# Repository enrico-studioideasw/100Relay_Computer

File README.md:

# 100Relay_Computer
A full calculator made with 100 relays 

Questo repository raccoglie lo sviluppo di un computer a relè realizzato con componenti facilmente reperibili. L'obiettivo non è ottenere prestazioni, ma costruire una macchina didattica completamente comprensibile: dalla logica cablata al microcodice, fino all'assembler e ai programmi di esempio.

Nella documentazione troverete foto, schema a blocchi della macchina, pcb e sch per eagle. 

Il risultato è:
Una scheda madre che raccoglie tutti i componenti separandone le unità logiche.
Una macchina con un microcodice minimale ma computazionalmente completo.
32 bytes di rom e 4 nibbles di ram (potenzialmente espandibili a 16). Programma in rome  ram per i dati. Nessun I/O ma un led per ciascuna cella di ram. 
Mantenendo la soglia dei 100 rele non credo sia possibile fare di meglio.

Semplificazioni:
I rele sono usati con logica positiva: "1" se c'e' abbastanza tensione da far scattare la bobina, "0" in tutti gli altri casi. Questo semplifica molto la progettazione.. e permette di abbinare facilmente OR e AND a diodi,  principalmente utilizzati per il microcodice.
La micro-ROM è realizzata mediante una matrice di socket femmina passo 2,54 mm. Il contenuto della ROM viene programmato inserendo o rimuovendo diodi nei socket, senza necessità di saldature e con il programma "a vista". 

Il mio scopo era stare sotto i  100 rele, usando componenti commerciali a basso costo. Ad oggi:
 4 rele DPDT per il clock a più fasi
12 rele DPDT per il program counter a 6 bit
19 rele per pilotare la ROM "a diodi". 
24 rele per la ram e 4 per la sua decodifica
18 rele per accumulatore, risultato, Instruction Register.
12 rele per la ALU
Il resto per microcodice e logiche varie. Quindi scopo non raggiunto ma macchina completa con esattamente 100 rele. Potremmo averne circa 90 con solo 16 bytes di rom, ma si rinuncia alla possibilita di programmi decenti. 

Ho dovuto ridurre all'osso il microcodice, quindi queste sono le Istruzioni:
HCF      0000XXXX (oops.. HALT) 
JZ DEST  11XXXXXX
LD       0110XXXX Load direct, azzera flag 
LDA      0100XXXX Load from ram addr 
SUM      0111XXXX somma ad A il conentuto della cella XXXX 
STA      1000XXXX copia A sulla cella indicata di ram

Una cella di ROM vuota causa immediatamente un HALT,  quindi senza programma la macchian si ferma subito (Halt and Catch Fire ..  forse)

Note:
- per decrementare A basta sommare F. 
- Per una jump basta qualcosa tipo: STA 3, LD 0, JZ XX, LDA 3  .. non ho uno stack ma qualcosa per mantenere A si fa lo stesso. Certo che più ram saebbe meglio.

qualche demo:
Faccina sorridente sui led di stato della ram:

LD 9
STA 0
LD 0
STA 1
LD 9
STA 2
LD 6
STA 3
HCF (oops.. HALT) 

Diagonale

LD 8
STA 0
LD 4
STA 1
LD 2
STA 2
LD 1
STA 3
HCF

Prodotto:
RAM0 = moltiplicando
RAM1 = moltiplicatore
RAM2 = risultato
RAMF = 15 (-1)
00 LD 0
01 STA 2          ; risultato = 0
LOOP:
02 LDA 1
03 JZ 13 - END          ; finito?
04 STA 3          ; salvo contatore
05 LDA 2
06 SUM 0
07 STA 2          ; risultato += moltiplicando
08 LDA 3
09 SUM F
10 STA 1          ; contatore--
11 JMP 02 LOOP
12 END: HCF (oops.. halt)

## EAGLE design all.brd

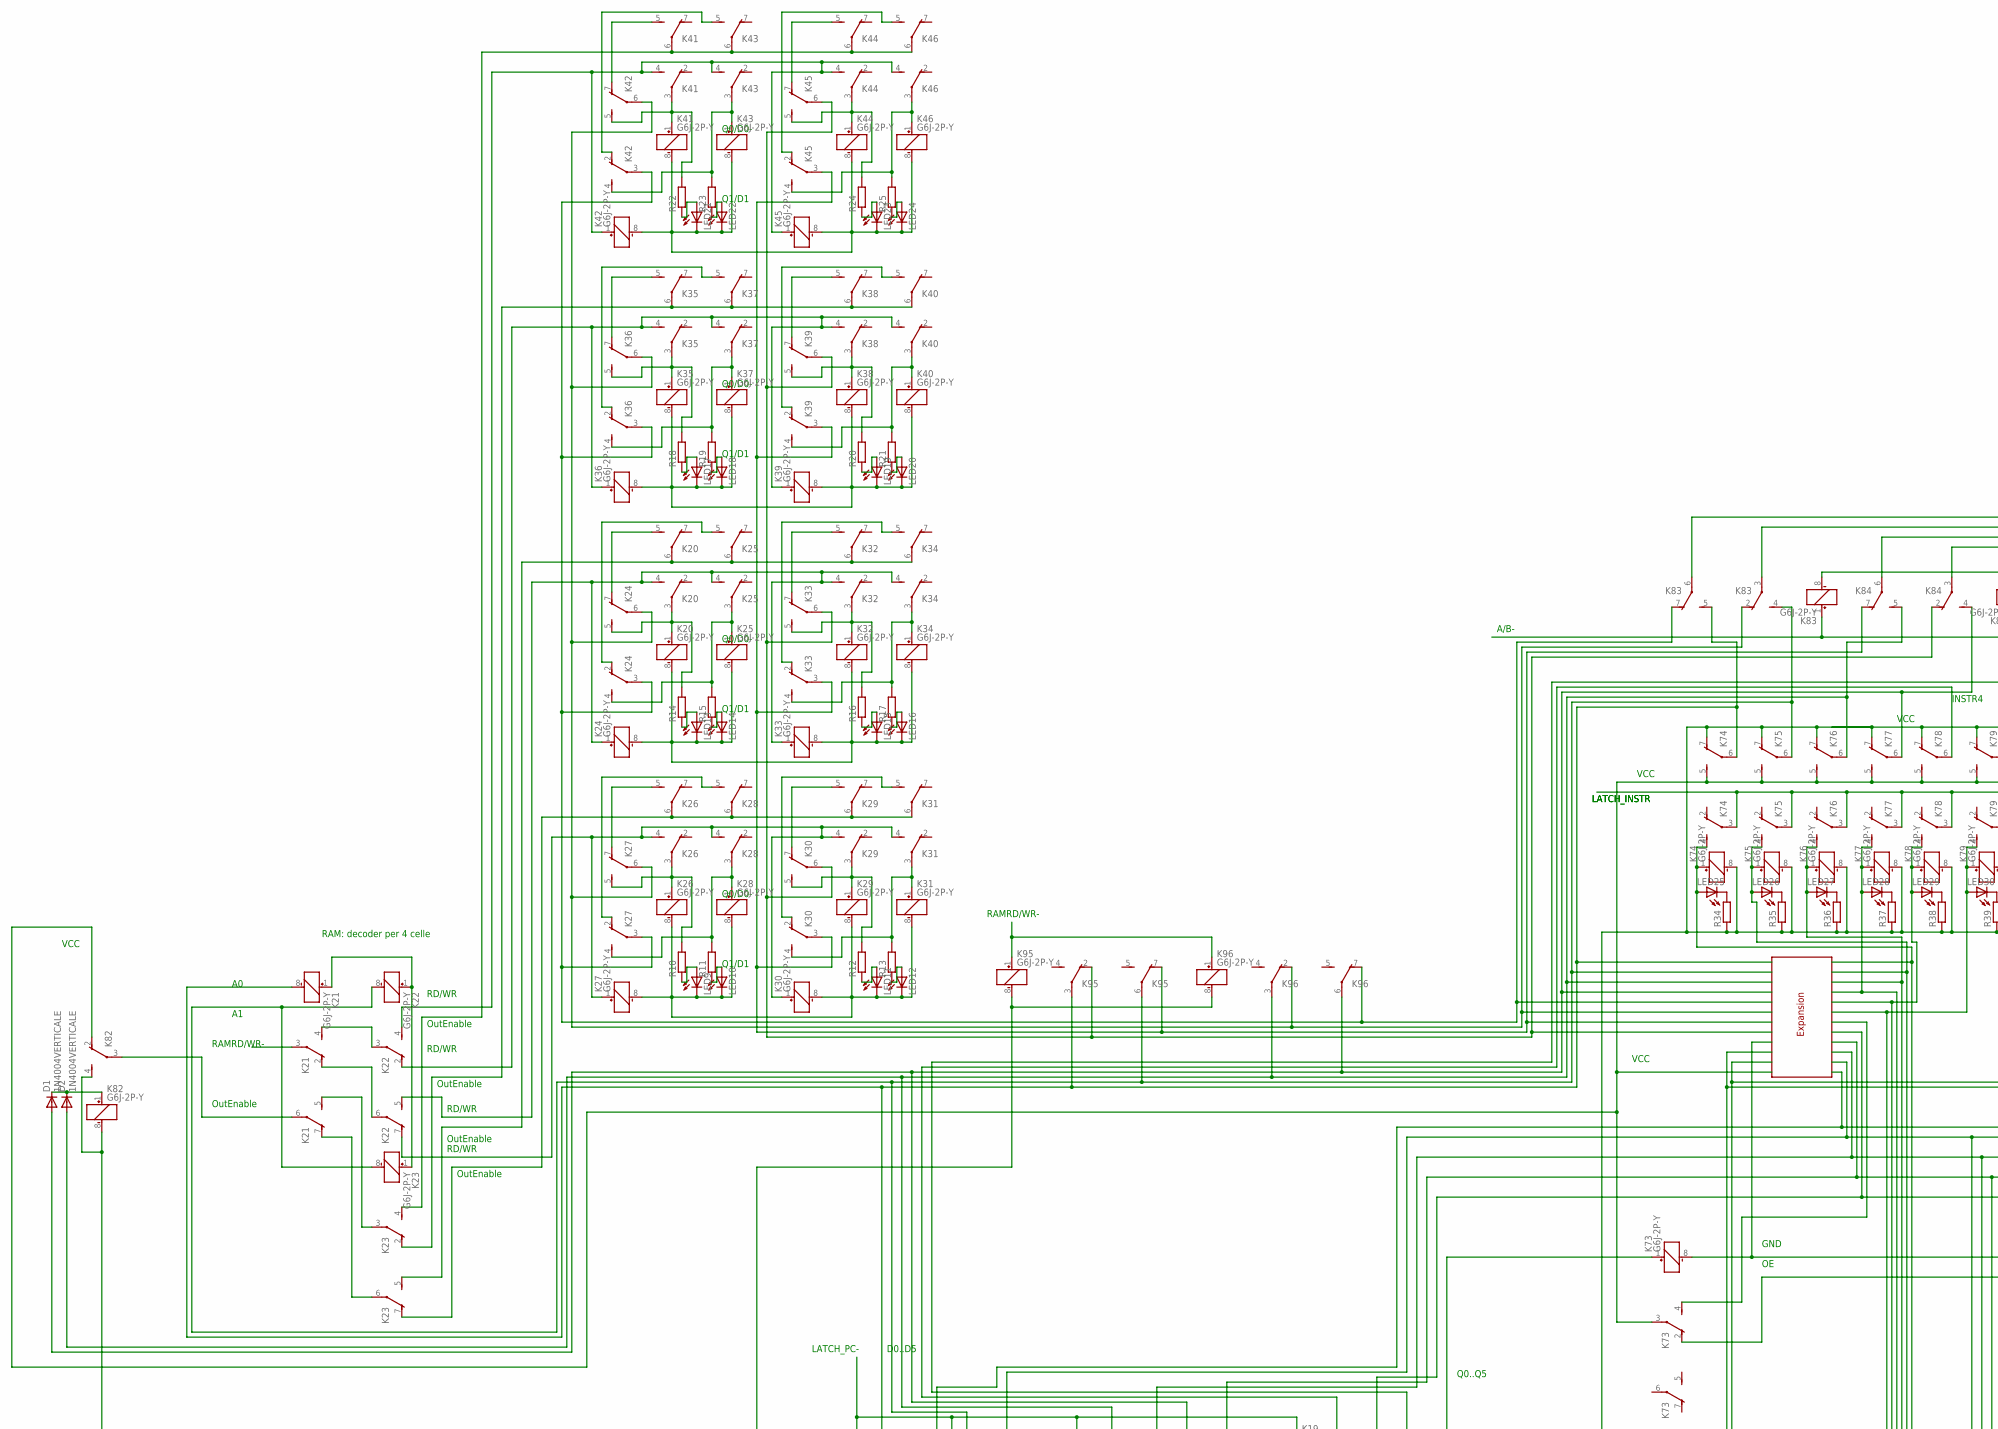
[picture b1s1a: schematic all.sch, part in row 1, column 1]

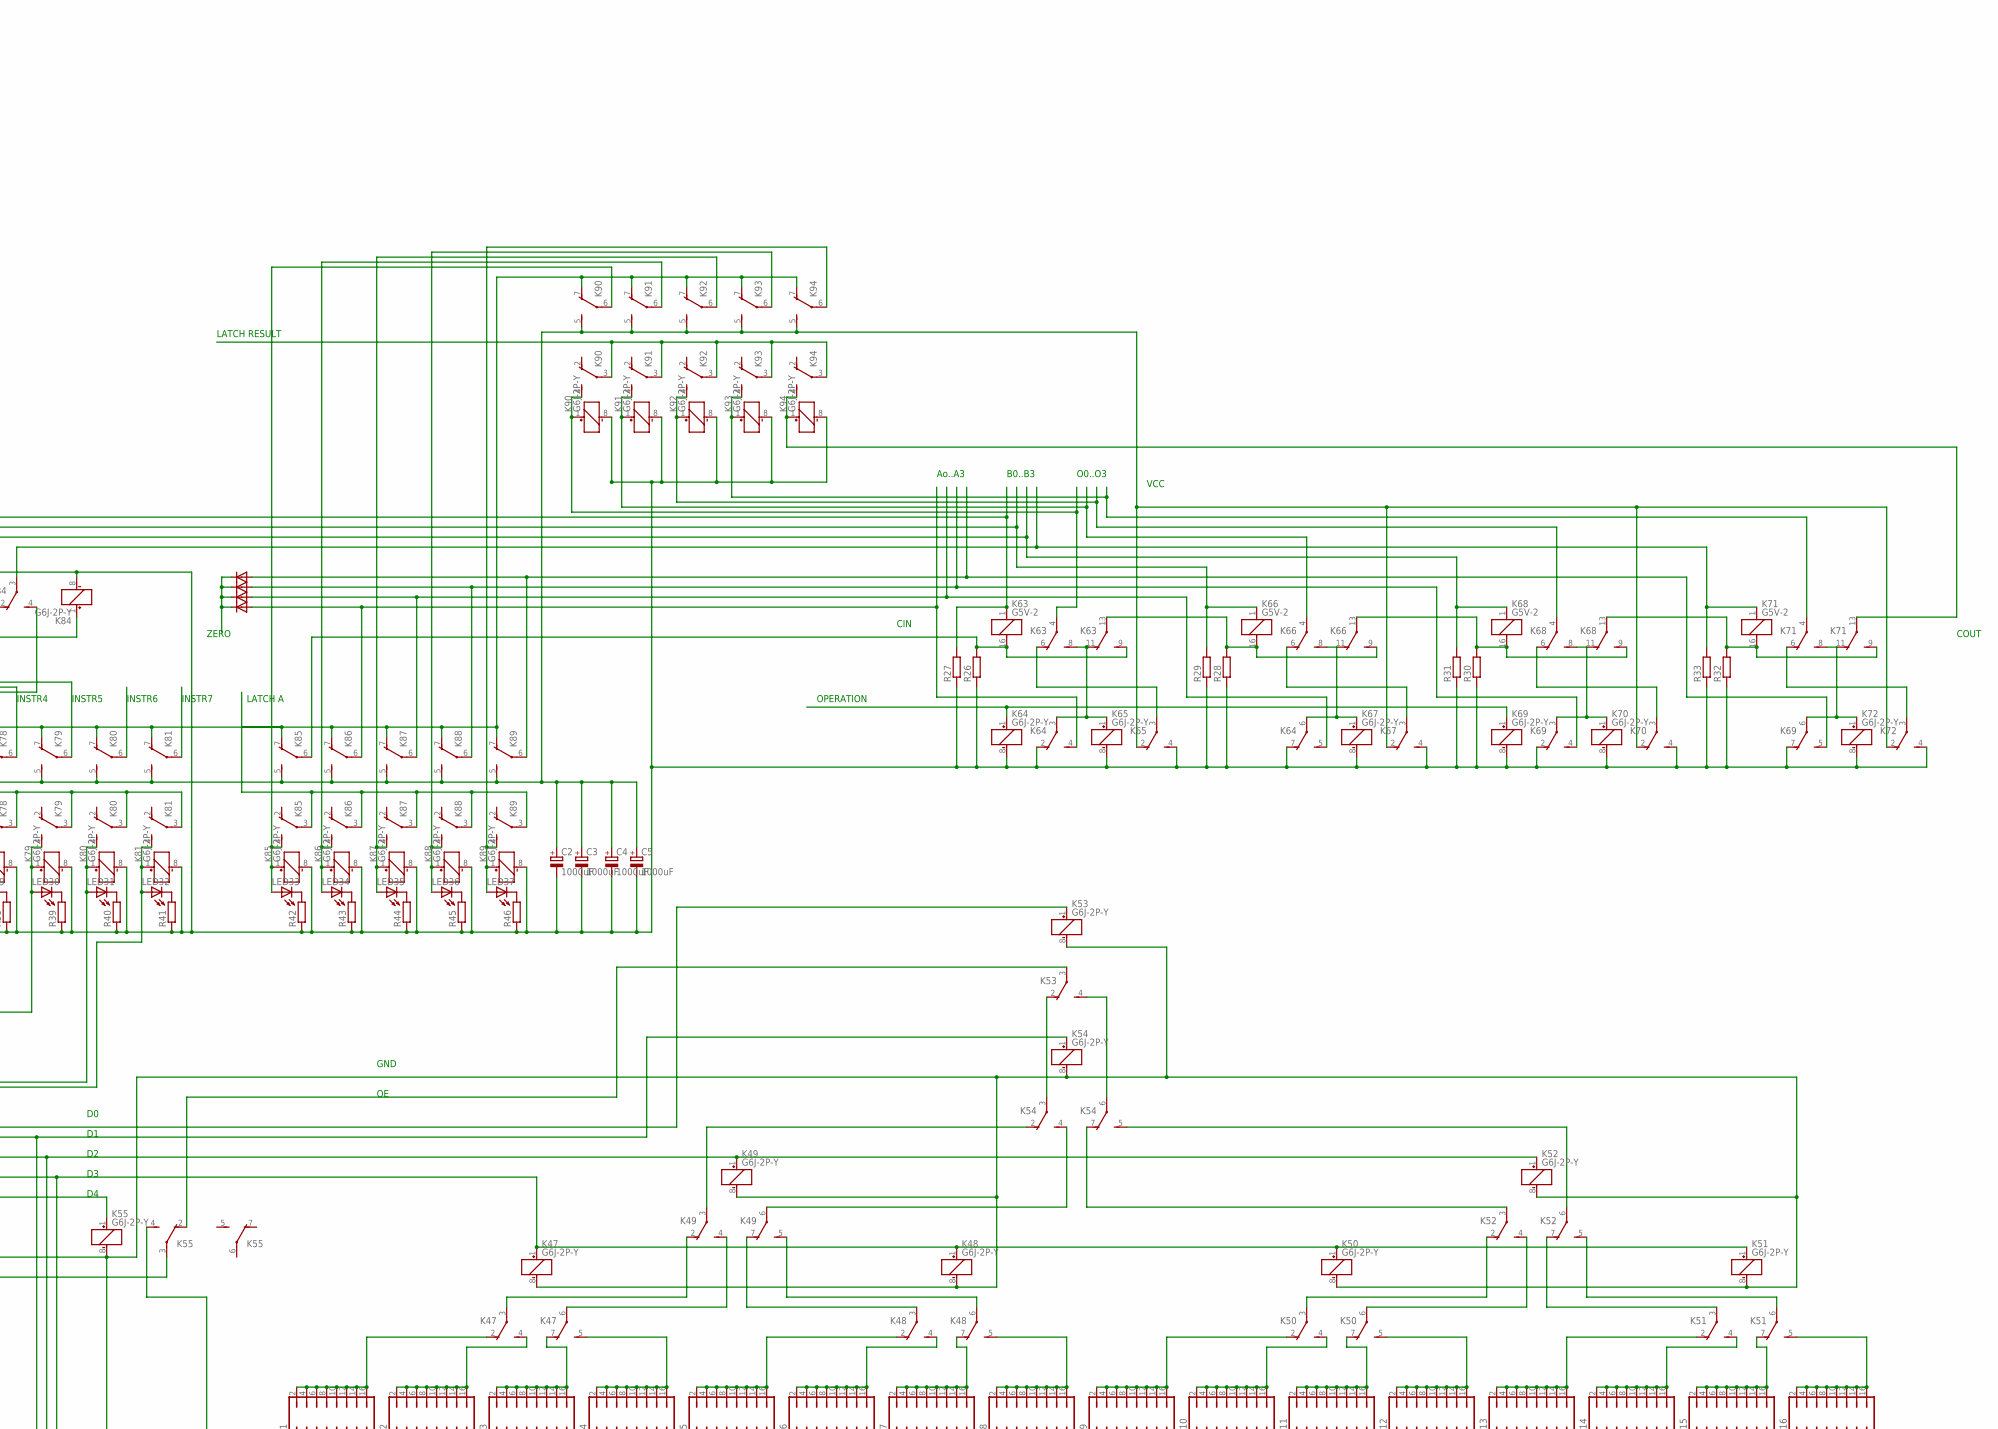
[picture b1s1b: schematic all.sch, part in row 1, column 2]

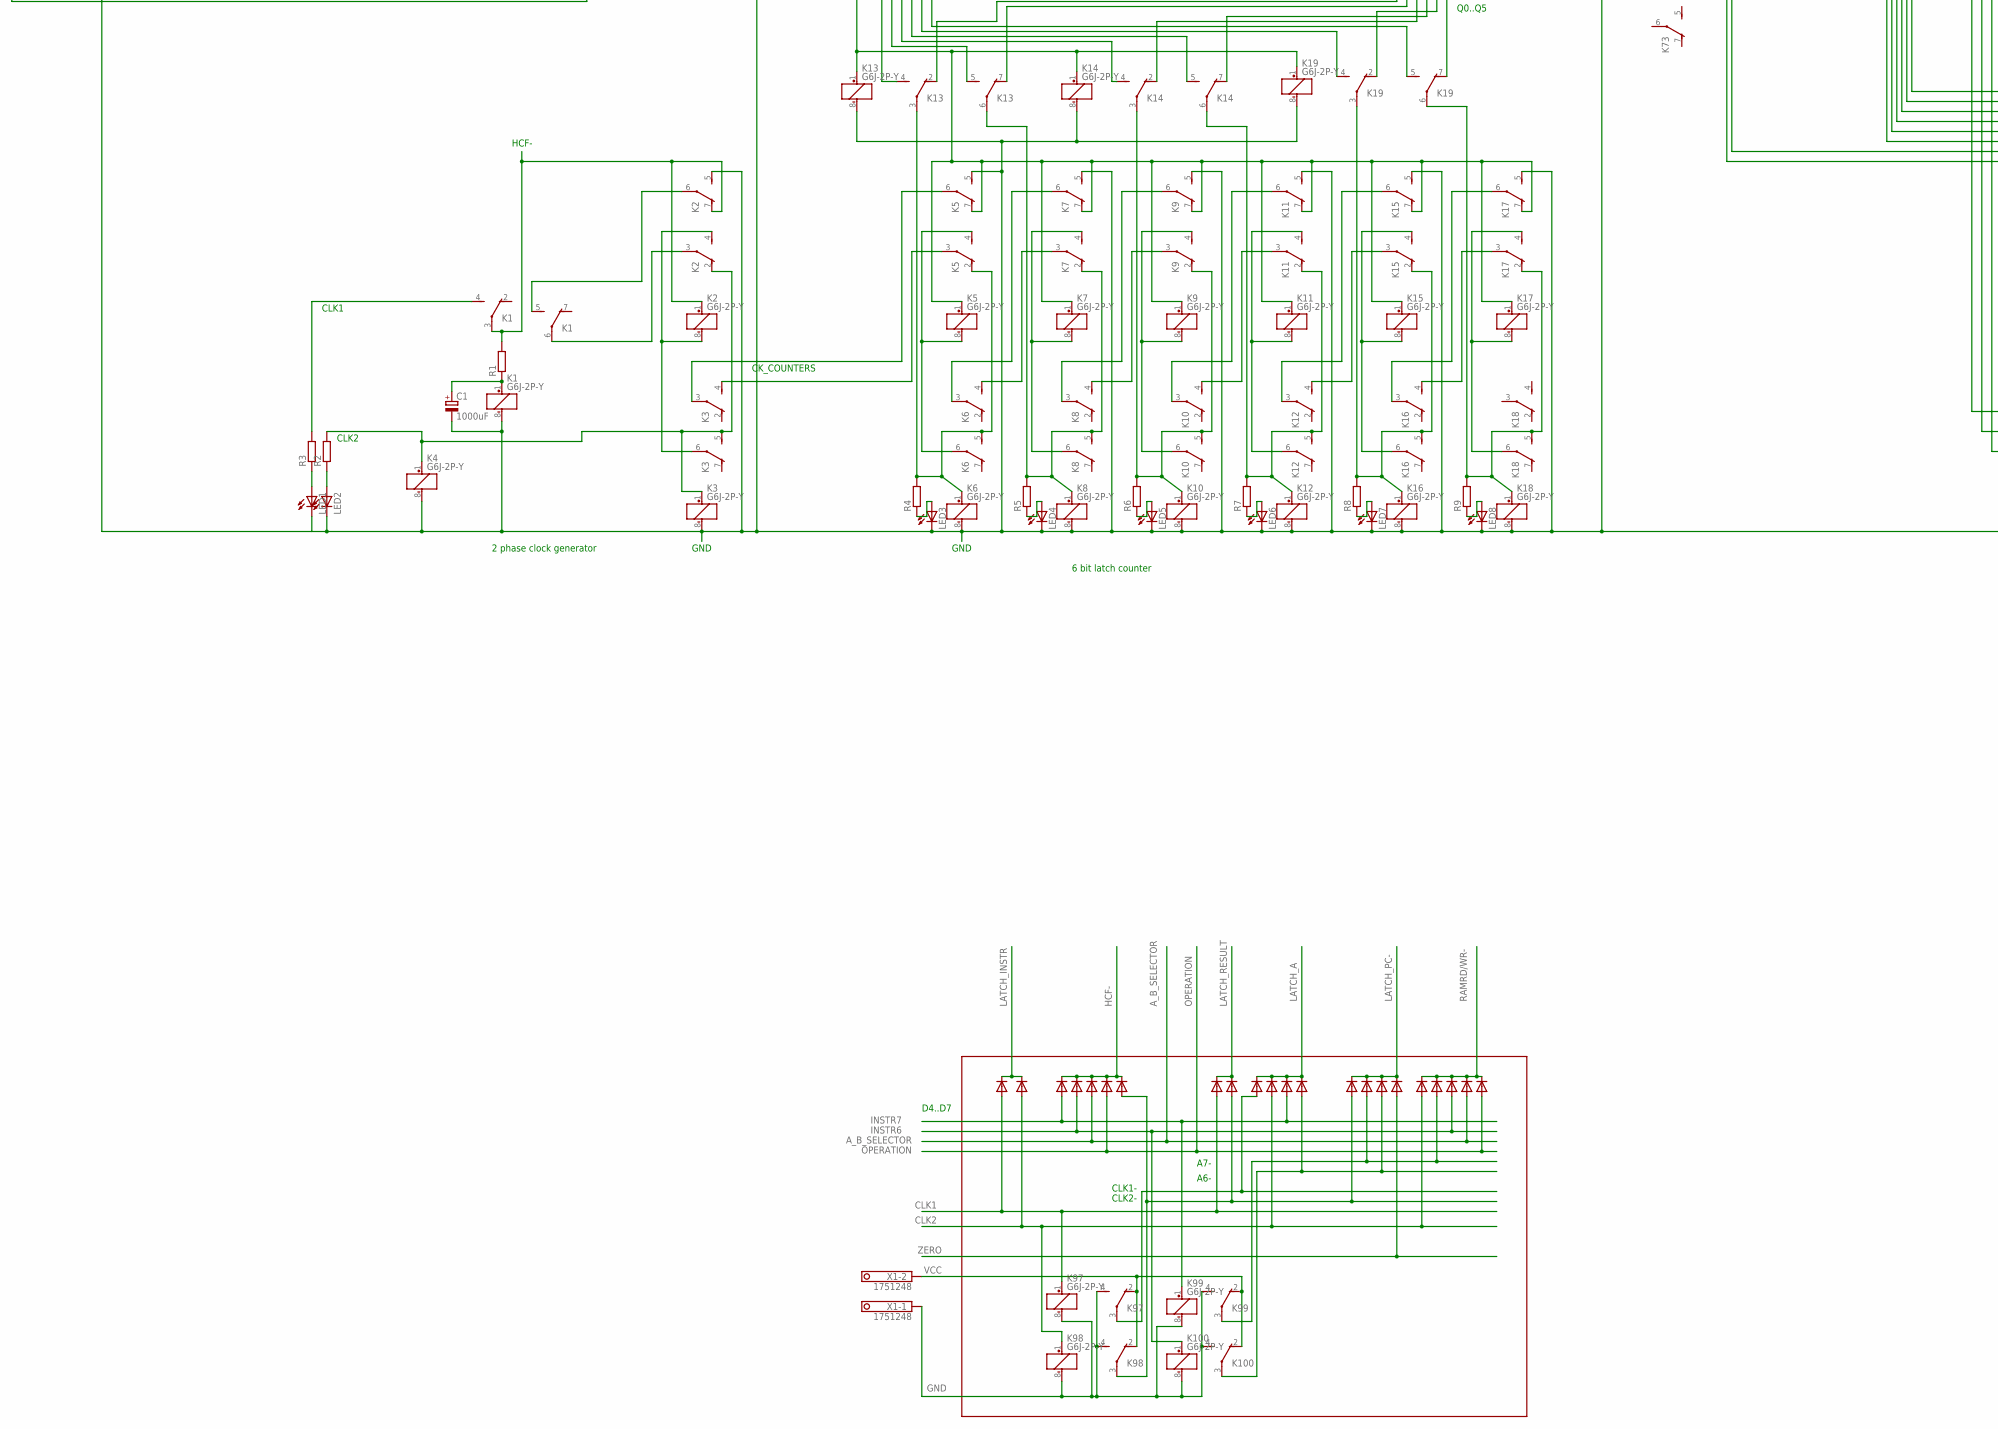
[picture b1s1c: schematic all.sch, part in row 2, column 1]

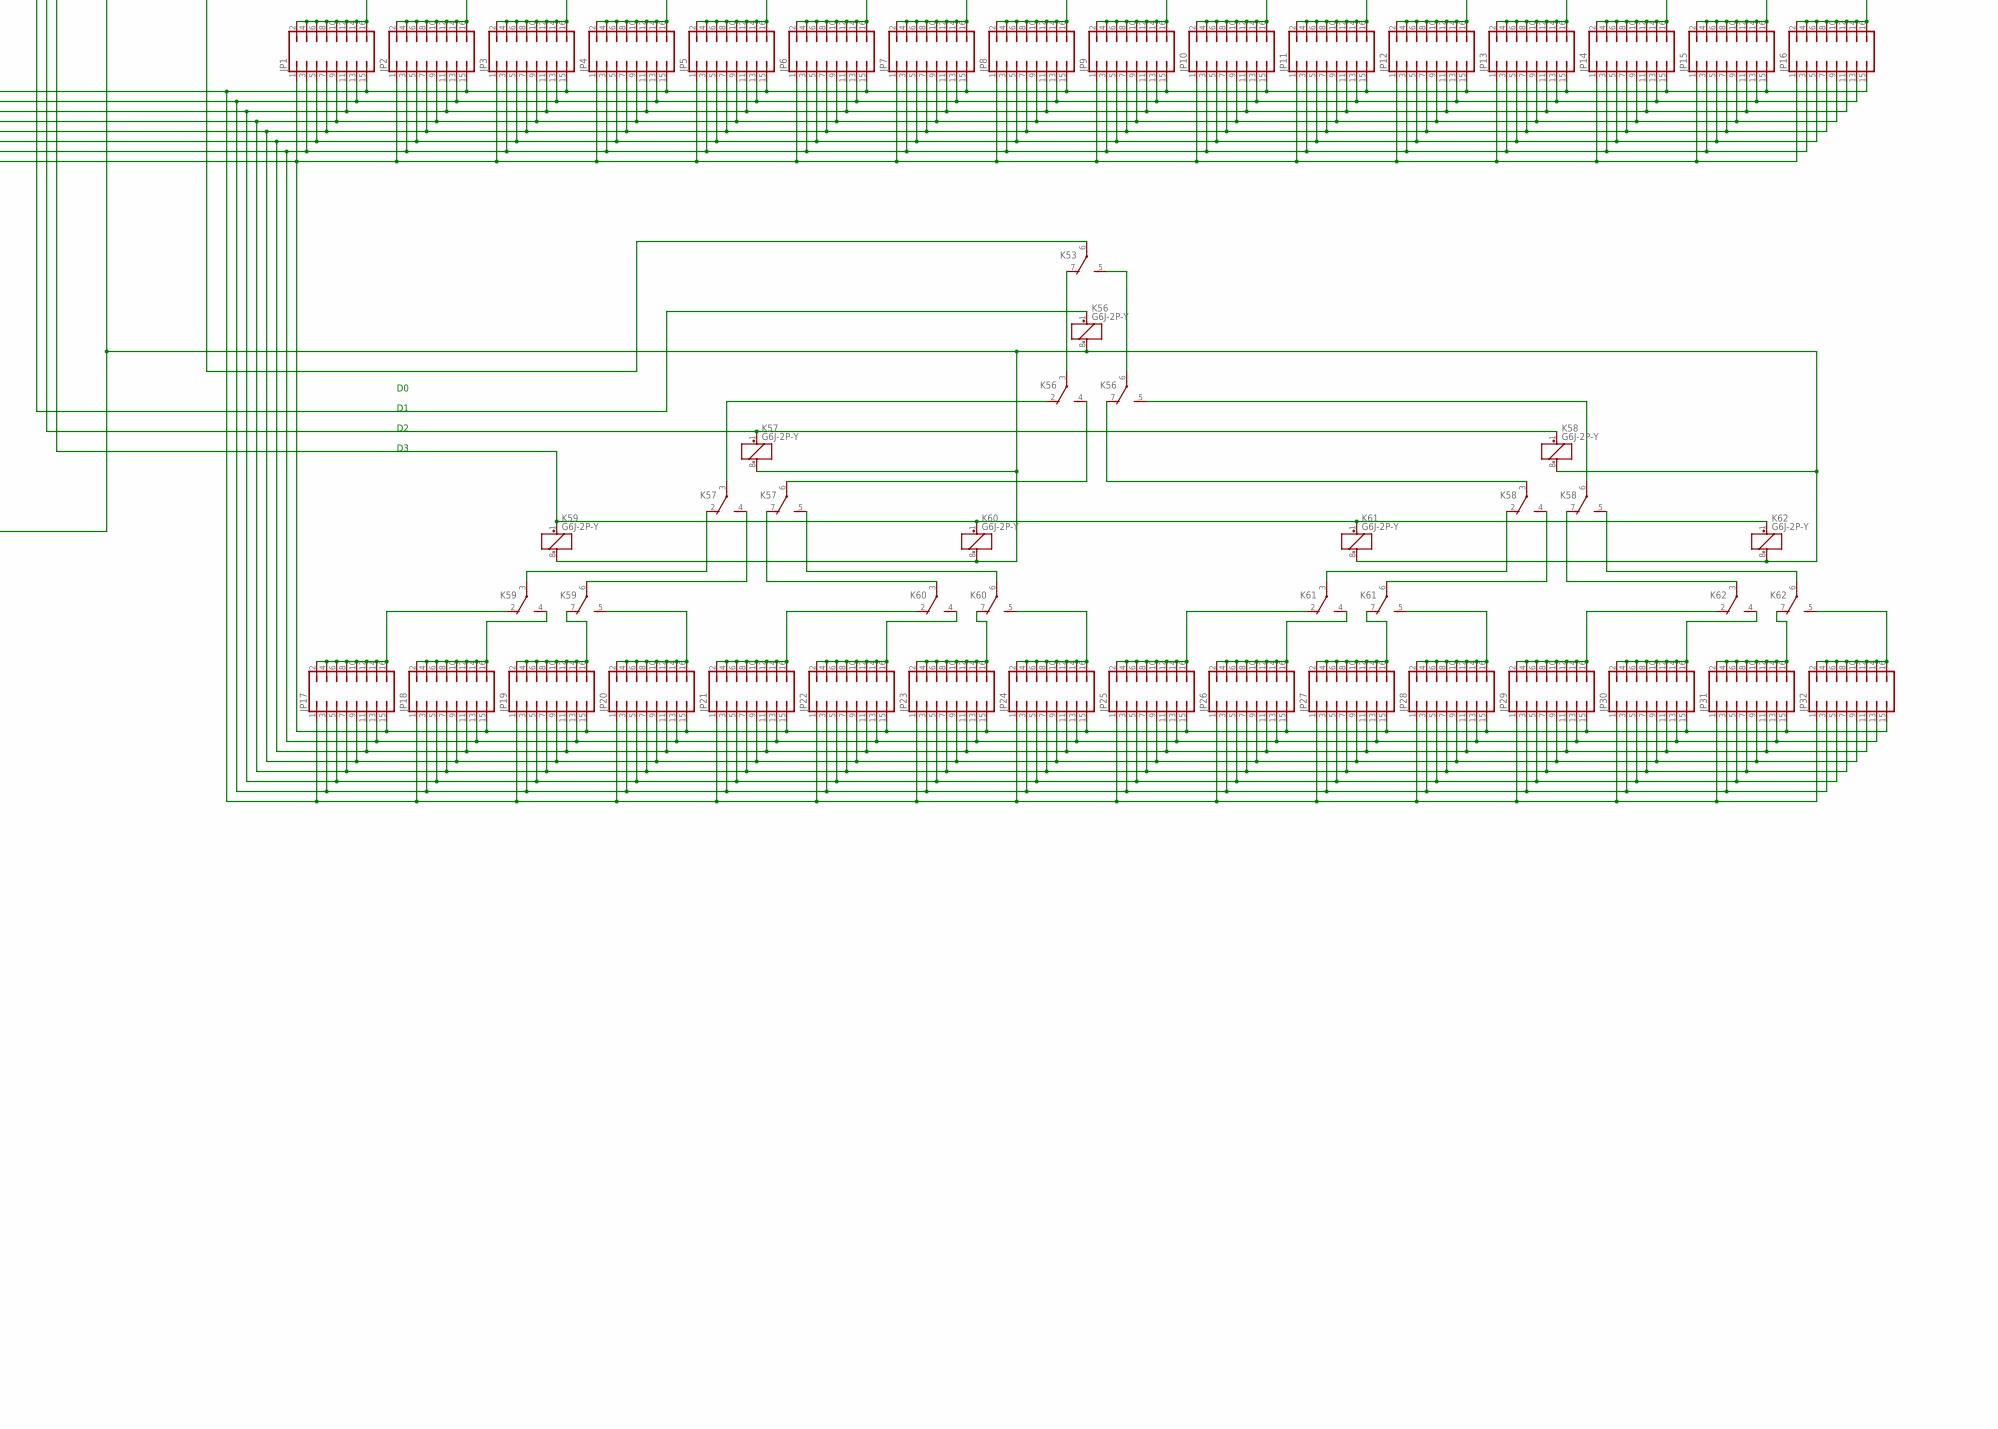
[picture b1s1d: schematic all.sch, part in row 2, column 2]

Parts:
C1: 1000uF; E5-10,5
C2, C3, C4, C5: 1000uF; E3,5-10
D1, D2, D3, D4, D5, D6, D29, D30, D31, D32, D33, D34, D35, D36, D37, D38, D39, D40, D41, D42, D43, D44, D45, D46, D47, D48, D49, D50: 1N4004VERTICALE; ZDIO-2.5
JP1, JP2, JP3, JP4, JP5, JP6, JP7, JP8, JP9, JP10, JP11, JP12, JP13, JP14, JP15, JP16, JP17, JP18, JP19, JP20, JP21, JP22, JP23, JP24, JP25, JP26, JP27, JP28, JP29, JP30, JP31, JP32: JP8Q
K1, K2, K3, K4, K5, K6, K7, K8, K9, K10, K11, K12, K13, K14, K15, K16, K17, K18, K19, K20, K21, K22, K23, K24, K25, K26, K27, K28, K29, K30, K31, K32, K33, K34, K35, K36, K37, K38, K39, K40, K41, K42, K43, K44, K45, K46, K47, K48, K49, K50, K51, K52, K53, K54, K55, K56, K57, K58, K59, K60, K61, K62, K64, K65, K67, K69, K70, K72, K73, K74, K75, K76, K77, K78, K79, K80, K81, K82, K83, K84, K85, K86, K87, K88, K89, K90, K91, K92, K93, K94, K95, K96, K97, K98, K99, K100: G6J-2P-Y
K63, K66, K68, K71: G5V-2
LED1, LED2, LED3, LED4, LED5, LED6, LED7, LED8, LED9, LED10, LED11, LED12, LED13, LED14, LED15, LED16, LED17, LED18, LED19, LED20, LED21, LED22, LED23, LED24: LED5MM
LED25, LED26, LED27, LED28, LED29, LED30, LED31, LED32, LED33, LED34, LED35, LED36, LED37: LED3MM
R1, R2, R3, R4, R5, R6, R7, R8, R9, R10, R11, R12, R13, R14, R15, R16, R17, R18, R19, R20, R21, R22, R23, R24, R25, R26, R27, R28, R29, R30, R31, R32, R33, R34, R35, R36, R37, R38, R39, R40, R41, R42, R43, R44, R45, R46: R-EU_0204/2V; 0204V
X1: 1751248

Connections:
A_B_SELECTOR: D33.A, D49.A, K83.1 (+), K84.1 (+)
CLK1: D29.A, D36.A, K1.4 (S), K97.1 (+), R3.2
CLK2: D30.A, D39.A, D46.A, K2.2 (O), K3.1 (+), K3.5 (S), K4.1 (+), K98.1 (+), R2.2
GND: C1.-, C2.-, C3.-, C4.-, C5.-, K1.8 (-), K2.5 (S), K3.8 (-), K4.8 (-), K5.5 (S), K6.8 (-), K7.5 (S), K8.8 (-), K9.5 (S), K10.8 (-), K11.5 (S), K12.8 (-), K13.8 (-), K14.8 (-), K15.5 (S), K16.8 (-), K17.5 (S), K18.8 (-), K19.8 (-), K47.8 (-), K48.8 (-), K49.8 (-), K50.8 (-), K51.8 (-), K52.8 (-), K53.8 (-), K54.8 (-), K55.8 (-), K56.8 (-), K57.8 (-), K58.8 (-), K59.8 (-), K60.8 (-), K61.8 (-), K62.8 (-), K64.2 (O), K64.7 (O), K64.8 (-), K65.4 (S), K65.8 (-), K67.4 (S), K67.8 (-), K69.2 (O), K69.7 (O), K69.8 (-), K70.4 (S), K70.8 (-), K72.4 (S), K72.8 (-), K73.8 (-), K74.7 (O), K74.8 (-), K75.7 (O), K75.8 (-), K76.7 (O), K76.8 (-), K77.7 (O), K77.8 (-), K78.7 (O), K78.8 (-), K79.7 (O), K79.8 (-), K80.7 (O), K80.8 (-), K81.7 (O), K81.8 (-), K82.4 (S), K82.8 (-), K83.8 (-), K84.8 (-), K85.7 (O), K85.8 (-), K86.7 (O), K86.8 (-), K87.7 (O), K87.8 (-), K88.7 (O), K88.8 (-), K89.7 (O), K89.8 (-), K90.7 (O), K90.8 (-), K91.7 (O), K91.8 (-), K92.7 (O), K92.8 (-), K93.7 (O), K93.8 (-), K94.7 (O), K94.8 (-), K95.8 (-), K96.8 (-), K97.4 (S), K97.8 (-), K98.4 (S), K98.8 (-), K99.4 (S), K99.8 (-), K100.4 (S), K100.8 (-), LED1.K (C), LED2.K (C), LED3.K (C), LED4.K (C), LED5.K (C), LED6.K (C), LED7.K (C), LED8.K (C), R26.1, R27.1, R28.1, R29.1, R30.1, R31.1, R32.1, R33.1, R34.1, R35.1, R36.1, R37.1, R38.1, R39.1, R40.1, R41.1, R42.1, R43.1, R44.1, R45.1, R46.1, X1.1
HCF-: D31.C, D32.C, D33.C, D34.C, D35.C, K1.3, K2.1 (+), K2.7 (O), R1.2
INSTR4: K19.4 (S), K78.6
INSTR5: K19.5 (S), K79.6
INSTR6: D32.A, D48.A, K80.6, K100.1 (+)
INSTR7: D31.A, D40.A, K81.6, K99.1 (+)
LATCH_A: D38.C, D39.C, D40.C, D41.C, K85.3, K86.3, K87.3, K88.3, K89.3
LATCH_INSTR: D29.C, D30.C, K74.3, K75.3, K76.3, K77.3, K78.3, K79.3, K80.3, K81.3
LATCH_PC-: D42.C, D43.C, D44.C, D45.C, K5.1 (+), K5.7 (O), K7.1 (+), K7.7 (O), K9.1 (+), K9.7 (O), K11.1 (+), K11.7 (O), K13.1 (+), K14.1 (+), K15.1 (+), K15.7 (O), K17.1 (+), K17.7 (O), K19.1 (+)
LATCH_RESULT: D36.C, D37.C, K90.3, K91.3, K92.3, K93.3, K94.3
unnamed: C1.+, K1.1 (+), R1.1
unnamed: K6.3, K7.6
unnamed: K6.4 (S), K7.3
unnamed: K1.5 (S), K2.6
unnamed: K1.6, K2.3
unnamed: D38.A, K97.3
unnamed: K63.9 (S), K63.16 (2), K85.6, R26.2
unnamed: D35.A, D37.A, D42.A, K98.3
unnamed: K2.4 (S), K2.8 (-), K3.6
unnamed: K3.4 (S), K5.3
unnamed: K3.3, K5.6
unnamed: K13.4 (S), K21.8 (-), K74.6, K83.5 (S), K95.3
unnamed: K19.2 (O), K55.1 (+)
unnamed: K12.3, K15.6
unnamed: K13.7 (O), K54.1 (+), K56.1 (+)
unnamed: K12.4 (S), K15.3
unnamed: K5.2 (O), K6.1 (+), K6.5 (S), K13.3, R4.2
unnamed: K5.4 (S), K5.8 (-), K6.6
unnamed: K13.5 (S), K22.8 (-), K23.8 (-), K75.6, K83.4 (S), K95.6
unnamed: K13.2 (O), K53.1 (+)
unnamed: D2.A, K14.4 (S), K76.6, K84.5 (S), K96.3
unnamed: K7.2 (O), K8.1 (+), K8.5 (S), K13.6, R5.2
unnamed: K7.4 (S), K7.8 (-), K8.6
unnamed: D1.A, K14.5 (S), K77.6, K84.4 (S), K96.6
unnamed: K14.2 (O), K49.1 (+), K52.1 (+), K57.1 (+), K58.1 (+)
unnamed: K8.3, K9.6
unnamed: K8.4 (S), K9.3
unnamed: K14.7 (O), K47.1 (+), K48.1 (+), K50.1 (+), K51.1 (+), K59.1 (+), K60.1 (+), K61.1 (+), K62.1 (+)
unnamed: K15.2 (O), K16.1 (+), K16.5 (S), K19.3, R8.2
unnamed: K9.2 (O), K10.1 (+), K10.5 (S), K14.3, R6.2
unnamed: K9.4 (S), K9.8 (-), K10.6
unnamed: K15.4 (S), K15.8 (-), K16.6
unnamed: K16.3, K17.6
unnamed: K10.3, K11.6
unnamed: K10.4 (S), K11.3
unnamed: K16.4 (S), K17.3
unnamed: K11.2 (O), K12.1 (+), K12.5 (S), K14.6, R7.2
unnamed: K11.4 (S), K11.8 (-), K12.6
unnamed: K19.7 (O), K73.1 (+)
unnamed: LED1.A, R3.1
unnamed: LED2.A, R2.1
unnamed: K17.2 (O), K18.1 (+), K18.5 (S), K19.6, R9.2
unnamed: K17.4 (S), K17.8 (-), K18.6
unnamed: LED9.A, R10.1
unnamed: D43.A, D47.A, K99.3
unnamed: D41.A, D44.A, K100.3
unnamed: LED3.A, R4.1
unnamed: LED4.A, R5.1
unnamed: LED5.A, R6.1
unnamed: LED6.A, R7.1
unnamed: LED7.A, R8.1
unnamed: LED8.A, R9.1
unnamed: LED10.A, R11.1
unnamed: LED11.A, R12.1
unnamed: LED12.A, R13.1
unnamed: K21.4 (S), K22.3
unnamed: K21.2 (O), K22.6
unnamed: K86.1 (+), K86.4 (S), K91.6, LED34.A
unnamed: K22.2 (O), K35.4 (S), K36.1 (+), K37.4 (S), K38.4 (S), K39.1 (+), K40.4 (S)
unnamed: K20.4 (S), K22.5 (S), K24.1 (+), K25.4 (S), K32.4 (S), K33.1 (+), K34.4 (S)
unnamed: K22.7 (O), K26.4 (S), K27.1 (+), K28.4 (S), K29.4 (S), K30.1 (+), K31.4 (S)
unnamed: K21.5 (S), K23.3
unnamed: K21.7 (O), K23.6
unnamed: K63.1, K83.6, R27.2
unnamed: K23.2 (O), K35.6, K37.6, K38.6, K40.6
unnamed: D6.A, K64.4 (S), K86.6
unnamed: K23.7 (O), K26.6, K28.6, K29.6, K31.6
unnamed: K21.6, K82.3
unnamed: K21.1 (+), K22.1 (+), K23.1 (+)
unnamed: K22.4 (S), K41.4 (S), K42.1 (+), K43.4 (S), K44.4 (S), K45.1 (+), K46.4 (S)
unnamed: K23.4 (S), K41.6, K43.6, K44.6, K46.6
unnamed: JP1.2, JP1.4, JP1.6, JP1.8, JP1.10, JP1.12, JP1.14, JP1.16, K47.2 (O)
unnamed: K20.6, K23.5 (S), K25.6, K32.6, K34.6
unnamed: K20.1 (+), K20.3, K24.5 (S), R14.2
unnamed: K26.1 (+), K26.3, K27.5 (S), R10.2
unnamed: K24.2 (O), K25.5 (S)
unnamed: K24.4 (S), K25.1 (+), K25.3, R15.2
unnamed: K20.5 (S), K24.7 (O)
unnamed: K27.2 (O), K28.5 (S)
unnamed: K27.4 (S), K28.1 (+), K28.3, R11.2
unnamed: K26.5 (S), K27.7 (O)
unnamed: K24.6, K27.6, K36.6, K42.6, K83.2 (O), K96.2 (O)
unnamed: K24.3, K27.3, K36.3, K42.3, K83.7 (O), K96.7 (O)
unnamed: K29.1 (+), K29.3, K30.5 (S), R12.2
unnamed: K26.8 (-), K27.8 (-), K28.8 (-), K29.8 (-), K30.8 (-), K31.8 (-), LED9.K (C), LED10.K (C), LED11.K (C), LED12.K (C)
unnamed: JP2.2, JP2.4, JP2.6, JP2.8, JP2.10, JP2.12, JP2.14, JP2.16, K47.4 (S)
unnamed: JP3.2, JP3.4, JP3.6, JP3.8, JP3.10, JP3.12, JP3.14, JP3.16, K47.7 (O)
unnamed: K30.2 (O), K31.5 (S)
unnamed: K30.4 (S), K31.1 (+), K31.3, R13.2
unnamed: K29.5 (S), K30.7 (O)
unnamed: K30.6, K33.6, K39.6, K45.6, K84.2 (O), K95.2 (O)
unnamed: K30.3, K33.3, K39.3, K45.3, K84.7 (O), K95.7 (O)
unnamed: K32.1 (+), K32.3, K33.5 (S), R16.2
unnamed: K20.8 (-), K24.8 (-), K25.8 (-), K32.8 (-), K33.8 (-), K34.8 (-), LED13.K (C), LED14.K (C), LED15.K (C), LED16.K (C)
unnamed: K33.2 (O), K34.5 (S)
unnamed: K33.4 (S), K34.1 (+), K34.3, R17.2
unnamed: K32.5 (S), K33.7 (O)
unnamed: JP4.2, JP4.4, JP4.6, JP4.8, JP4.10, JP4.12, JP4.14, JP4.16, K47.5 (S)
unnamed: JP5.2, JP5.4, JP5.6, JP5.8, JP5.10, JP5.12, JP5.14, JP5.16, K48.2 (O)
unnamed: LED13.A, R14.1
unnamed: LED14.A, R15.1
unnamed: LED15.A, R16.1
unnamed: LED16.A, R17.1
unnamed: JP8.2, JP8.4, JP8.6, JP8.8, JP8.10, JP8.12, JP8.14, JP8.16, K48.5 (S)
unnamed: JP7.2, JP7.4, JP7.6, JP7.8, JP7.10, JP7.12, JP7.14, JP7.16, K48.7 (O)
unnamed: K35.1 (+), K35.3, K36.5 (S), R18.2
unnamed: K36.2 (O), K37.5 (S)
unnamed: K36.4 (S), K37.1 (+), K37.3, R19.2
unnamed: K35.5 (S), K36.7 (O)
unnamed: JP6.2, JP6.4, JP6.6, JP6.8, JP6.10, JP6.12, JP6.14, JP6.16, K48.4 (S)
unnamed: K47.6, K49.4 (S)
unnamed: K38.1 (+), K38.3, K39.5 (S), R20.2
unnamed: K35.8 (-), K36.8 (-), K37.8 (-), K38.8 (-), K39.8 (-), K40.8 (-), LED17.K (C), LED18.K (C), LED19.K (C), LED20.K (C)
unnamed: K39.2 (O), K40.5 (S)
unnamed: K39.4 (S), K40.1 (+), K40.3, R21.2
unnamed: K38.5 (S), K39.7 (O)
unnamed: K47.3, K49.2 (O)
unnamed: K48.3, K49.7 (O)
unnamed: LED17.A, R18.1
unnamed: LED18.A, R19.1
unnamed: LED19.A, R20.1
unnamed: LED20.A, R21.1
unnamed: K48.6, K49.5 (S)
unnamed: K55.3, K73.2 (O)
unnamed: K41.1 (+), K41.3, K42.5 (S), R22.2
unnamed: K42.2 (O), K43.5 (S)
unnamed: K42.4 (S), K43.1 (+), K43.3, R23.2
unnamed: K41.5 (S), K42.7 (O)
unnamed: K63.8 (S), K63.11 (O), K64.3, K65.1 (+)
unnamed: K44.1 (+), K44.3, K45.5 (S), R24.2
unnamed: K41.8 (-), K42.8 (-), K43.8 (-), K44.8 (-), K45.8 (-), K46.8 (-), LED21.K (C), LED22.K (C), LED23.K (C), LED24.K (C)
unnamed: K45.2 (O), K46.5 (S)
unnamed: K45.4 (S), K46.1 (+), K46.3, R25.2
unnamed: K44.5 (S), K45.7 (O)
unnamed: K63.4, K90.1 (+), K90.4 (S)
unnamed: K63.6 (O), K65.3
unnamed: LED21.A, R22.1
unnamed: LED22.A, R23.1
unnamed: LED23.A, R24.1
unnamed: LED24.A, R25.1
unnamed: K63.13, K66.9 (S), K66.16 (2), R28.2
unnamed: K66.1, K83.3, R29.2
unnamed: D5.A, K64.5 (S), K87.6
unnamed: K64.6, K66.8 (S), K66.11 (O), K67.1 (+)
unnamed: JP9.2, JP9.4, JP9.6, JP9.8, JP9.10, JP9.12, JP9.14, JP9.16, K50.2 (O)
unnamed: JP10.2, JP10.4, JP10.6, JP10.8, JP10.10, JP10.12, JP10.14, JP10.16, K50.4 (S)
unnamed: JP11.2, JP11.4, JP11.6, JP11.8, JP11.10, JP11.12, JP11.14, JP11.16, K50.7 (O)
unnamed: JP12.2, JP12.4, JP12.6, JP12.8, JP12.10, JP12.12, JP12.14, JP12.16, K50.5 (S)
unnamed: JP13.2, JP13.4, JP13.6, JP13.8, JP13.10, JP13.12, JP13.14, JP13.16, K51.2 (O)
unnamed: JP16.2, JP16.4, JP16.6, JP16.8, JP16.10, JP16.12, JP16.14, JP16.16, K51.5 (S)
unnamed: JP15.2, JP15.4, JP15.6, JP15.8, JP15.10, JP15.12, JP15.14, JP15.16, K51.7 (O)
unnamed: JP14.2, JP14.4, JP14.6, JP14.8, JP14.10, JP14.12, JP14.14, JP14.16, K51.4 (S)
unnamed: K50.6, K52.4 (S)
unnamed: K50.3, K52.2 (O)
unnamed: K51.3, K52.7 (O)
unnamed: K51.6, K52.5 (S)
unnamed: K49.6, K54.4 (S)
unnamed: K49.3, K54.2 (O)
unnamed: K52.3, K54.7 (O)
unnamed: K52.6, K54.5 (S)
unnamed: K53.2 (O), K54.3
unnamed: K53.4 (S), K54.6
unnamed: K53.3, K55.2 (O)
unnamed: JP1.15, JP2.15, JP3.15, JP4.15, JP5.15, JP6.15, JP7.15, JP8.15, JP9.15, JP10.15, JP11.15, JP12.15, JP13.15, JP14.15, JP15.15, JP16.15, JP17.1, JP18.1, JP19.1, JP20.1, JP21.1, JP22.1, JP23.1, JP24.1, JP25.1, JP26.1, JP27.1, JP28.1, JP29.1, JP30.1, JP31.1, JP32.1, K74.1 (+), K74.4 (S), LED25.A
unnamed: JP1.13, JP2.13, JP3.13, JP4.13, JP5.13, JP6.13, JP7.13, JP8.13, JP9.13, JP10.13, JP11.13, JP12.13, JP13.13, JP14.13, JP15.13, JP16.13, JP17.3, JP18.3, JP19.3, JP20.3, JP21.3, JP22.3, JP23.3, JP24.3, JP25.3, JP26.3, JP27.3, JP28.3, JP29.3, JP30.3, JP31.3, JP32.3, K75.1 (+), K75.4 (S), LED26.A
unnamed: JP17.2, JP17.4, JP17.6, JP17.8, JP17.10, JP17.12, JP17.14, JP17.16, K59.2 (O)
unnamed: JP18.2, JP18.4, JP18.6, JP18.8, JP18.10, JP18.12, JP18.14, JP18.16, K59.4 (S)
unnamed: JP19.2, JP19.4, JP19.6, JP19.8, JP19.10, JP19.12, JP19.14, JP19.16, K59.7 (O)
unnamed: JP20.2, JP20.4, JP20.6, JP20.8, JP20.10, JP20.12, JP20.14, JP20.16, K59.5 (S)
unnamed: JP21.2, JP21.4, JP21.6, JP21.8, JP21.10, JP21.12, JP21.14, JP21.16, K60.2 (O)
unnamed: JP24.2, JP24.4, JP24.6, JP24.8, JP24.10, JP24.12, JP24.14, JP24.16, K60.5 (S)
unnamed: JP23.2, JP23.4, JP23.6, JP23.8, JP23.10, JP23.12, JP23.14, JP23.16, K60.7 (O)
unnamed: JP22.2, JP22.4, JP22.6, JP22.8, JP22.10, JP22.12, JP22.14, JP22.16, K60.4 (S)
unnamed: K57.4 (S), K59.6
unnamed: K57.2 (O), K59.3
unnamed: K57.7 (O), K60.3
unnamed: K57.5 (S), K60.6
unnamed: JP1.11, JP2.11, JP3.11, JP4.11, JP5.11, JP6.11, JP7.11, JP8.11, JP9.11, JP10.11, JP11.11, JP12.11, JP13.11, JP14.11, JP15.11, JP16.11, JP17.5, JP18.5, JP19.5, JP20.5, JP21.5, JP22.5, JP23.5, JP24.5, JP25.5, JP26.5, JP27.5, JP28.5, JP29.5, JP30.5, JP31.5, JP32.5, K76.1 (+), K76.4 (S), LED27.A
unnamed: JP1.1, JP2.1, JP3.1, JP4.1, JP5.1, JP6.1, JP7.1, JP8.1, JP9.1, JP10.1, JP11.1, JP12.1, JP13.1, JP14.1, JP15.1, JP16.1, JP17.15, JP18.15, JP19.15, JP20.15, JP21.15, JP22.15, JP23.15, JP24.15, JP25.15, JP26.15, JP27.15, JP28.15, JP29.15, JP30.15, JP31.15, JP32.15, K81.1 (+), K81.4 (S), LED32.A
unnamed: JP1.3, JP2.3, JP3.3, JP4.3, JP5.3, JP6.3, JP7.3, JP8.3, JP9.3, JP10.3, JP11.3, JP12.3, JP13.3, JP14.3, JP15.3, JP16.3, JP17.13, JP18.13, JP19.13, JP20.13, JP21.13, JP22.13, JP23.13, JP24.13, JP25.13, JP26.13, JP27.13, JP28.13, JP29.13, JP30.13, JP31.13, JP32.13, K80.1 (+), K80.4 (S), LED31.A
unnamed: D1.C, D2.C, K82.1 (+)
unnamed: JP1.9, JP2.9, JP3.9, JP4.9, JP5.9, JP6.9, JP7.9, JP8.9, JP9.9, JP10.9, JP11.9, JP12.9, JP13.9, JP14.9, JP15.9, JP16.9, JP17.7, JP18.7, JP19.7, JP20.7, JP21.7, JP22.7, JP23.7, JP24.7, JP25.7, JP26.7, JP27.7, JP28.7, JP29.7, JP30.7, JP31.7, JP32.7, K77.1 (+), K77.4 (S), LED28.A
unnamed: JP25.2, JP25.4, JP25.6, JP25.8, JP25.10, JP25.12, JP25.14, JP25.16, K61.2 (O)
unnamed: JP26.2, JP26.4, JP26.6, JP26.8, JP26.10, JP26.12, JP26.14, JP26.16, K61.4 (S)
unnamed: JP27.2, JP27.4, JP27.6, JP27.8, JP27.10, JP27.12, JP27.14, JP27.16, K61.7 (O)
unnamed: JP28.2, JP28.4, JP28.6, JP28.8, JP28.10, JP28.12, JP28.14, JP28.16, K61.5 (S)
unnamed: JP29.2, JP29.4, JP29.6, JP29.8, JP29.10, JP29.12, JP29.14, JP29.16, K62.2 (O)
unnamed: JP32.2, JP32.4, JP32.6, JP32.8, JP32.10, JP32.12, JP32.14, JP32.16, K62.5 (S)
unnamed: JP31.2, JP31.4, JP31.6, JP31.8, JP31.10, JP31.12, JP31.14, JP31.16, K62.7 (O)
unnamed: JP30.2, JP30.4, JP30.6, JP30.8, JP30.10, JP30.12, JP30.14, JP30.16, K62.4 (S)
unnamed: K58.4 (S), K61.6
unnamed: K58.2 (O), K61.3
unnamed: K58.7 (O), K62.3
unnamed: K58.5 (S), K62.6
unnamed: K56.4 (S), K57.6
unnamed: K56.2 (O), K57.3
unnamed: K56.7 (O), K58.3
unnamed: K56.5 (S), K58.6
unnamed: K53.7 (O), K56.3
unnamed: K53.5 (S), K56.6
unnamed: K53.6, K55.4 (S)
unnamed: K66.4, K91.1 (+), K91.4 (S)
unnamed: K66.6 (O), K67.3
unnamed: K66.13, K68.9 (S), K68.16 (2), R30.2
unnamed: K68.1, K84.6, R31.2
unnamed: D4.A, K69.4 (S), K88.6
unnamed: K68.8 (S), K68.11 (O), K69.3, K70.1 (+)
unnamed: K68.4, K92.1 (+), K92.4 (S)
unnamed: K68.6 (O), K70.3
unnamed: K68.13, K71.9 (S), K71.16 (2), R32.2
unnamed: K71.1, K84.3, R33.2
unnamed: D3.A, K69.5 (S), K89.6
unnamed: K69.6, K71.8 (S), K71.11 (O), K72.1 (+)
unnamed: K71.13, K94.1 (+), K94.4 (S)
unnamed: K71.4, K93.1 (+), K93.4 (S)
unnamed: K71.6 (O), K72.3
unnamed: K89.1 (+), K89.4 (S), K94.6, LED37.A
unnamed: K88.1 (+), K88.4 (S), K93.6, LED36.A
unnamed: LED25.K (C), R34.2
unnamed: LED26.K (C), R35.2
unnamed: LED27.K (C), R36.2
unnamed: LED28.K (C), R37.2
unnamed: JP1.7, JP2.7, JP3.7, JP4.7, JP5.7, JP6.7, JP7.7, JP8.7, JP9.7, JP10.7, JP11.7, JP12.7, JP13.7, JP14.7, JP15.7, JP16.7, JP17.9, JP18.9, JP19.9, JP20.9, JP21.9, JP22.9, JP23.9, JP24.9, JP25.9, JP26.9, JP27.9, JP28.9, JP29.9, JP30.9, JP31.9, JP32.9, K78.1 (+), K78.4 (S), LED29.A
unnamed: JP1.5, JP2.5, JP3.5, JP4.5, JP5.5, JP6.5, JP7.5, JP8.5, JP9.5, JP10.5, JP11.5, JP12.5, JP13.5, JP14.5, JP15.5, JP16.5, JP17.11, JP18.11, JP19.11, JP20.11, JP21.11, JP22.11, JP23.11, JP24.11, JP25.11, JP26.11, JP27.11, JP28.11, JP29.11, JP30.11, JP31.11, JP32.11, K79.1 (+), K79.4 (S), LED30.A
unnamed: LED29.K (C), R38.2
unnamed: LED30.K (C), R39.2
unnamed: LED31.K (C), R40.2
unnamed: LED32.K (C), R41.2
unnamed: K87.1 (+), K87.4 (S), K92.6, LED35.A
unnamed: LED33.K (C), R42.2
unnamed: LED34.K (C), R43.2
unnamed: LED35.K (C), R44.2
unnamed: LED36.K (C), R45.2
unnamed: LED37.K (C), R46.2
unnamed: K85.1 (+), K85.4 (S), K90.6, LED33.A
OPERATION: D34.A, D50.A, K64.1 (+), K69.1 (+)
RAMRD/WR-: D46.C, D47.C, D48.C, D49.C, D50.C, K21.3, K95.1 (+), K96.1 (+)
VCC: C2.+, C3.+, C4.+, C5.+, K65.2 (O), K67.2 (O), K70.2 (O), K72.2 (O), K73.3, K74.5 (S), K75.5 (S), K76.5 (S), K77.5 (S), K78.5 (S), K79.5 (S), K80.5 (S), K81.5 (S), K82.2 (O), K85.5 (S), K86.5 (S), K87.5 (S), K88.5 (S), K89.5 (S), K90.5 (S), K91.5 (S), K92.5 (S), K93.5 (S), K94.5 (S), K97.2 (O), K98.2 (O), K99.2 (O), K100.2 (O), X1.2
ZERO: D3.C, D4.C, D5.C, D6.C, D45.A

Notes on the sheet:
GND
CK_COUNTERS
2 phase clock generator
LATCH_PC-
D0..D5
Q0..Q5
6 bit latch counter
RAMRD/WR-
RD/WR
OutEnable
RAM: decoder per 4 celle
Q0/D0-
Q1/D1
Ao..A3
B0..B3
O0..O3
CIN
VCC
COUT
A/B-
LATCH A
LATCH RESULT
OPERATION
CLK2
CLK1
ZERO
INSTR4
INSTR5
INSTR6
INSTR7
LATCH_INSTR
HCF-
CLK1-
CLK2-
A7-
A6-
D4..D7
Expansion

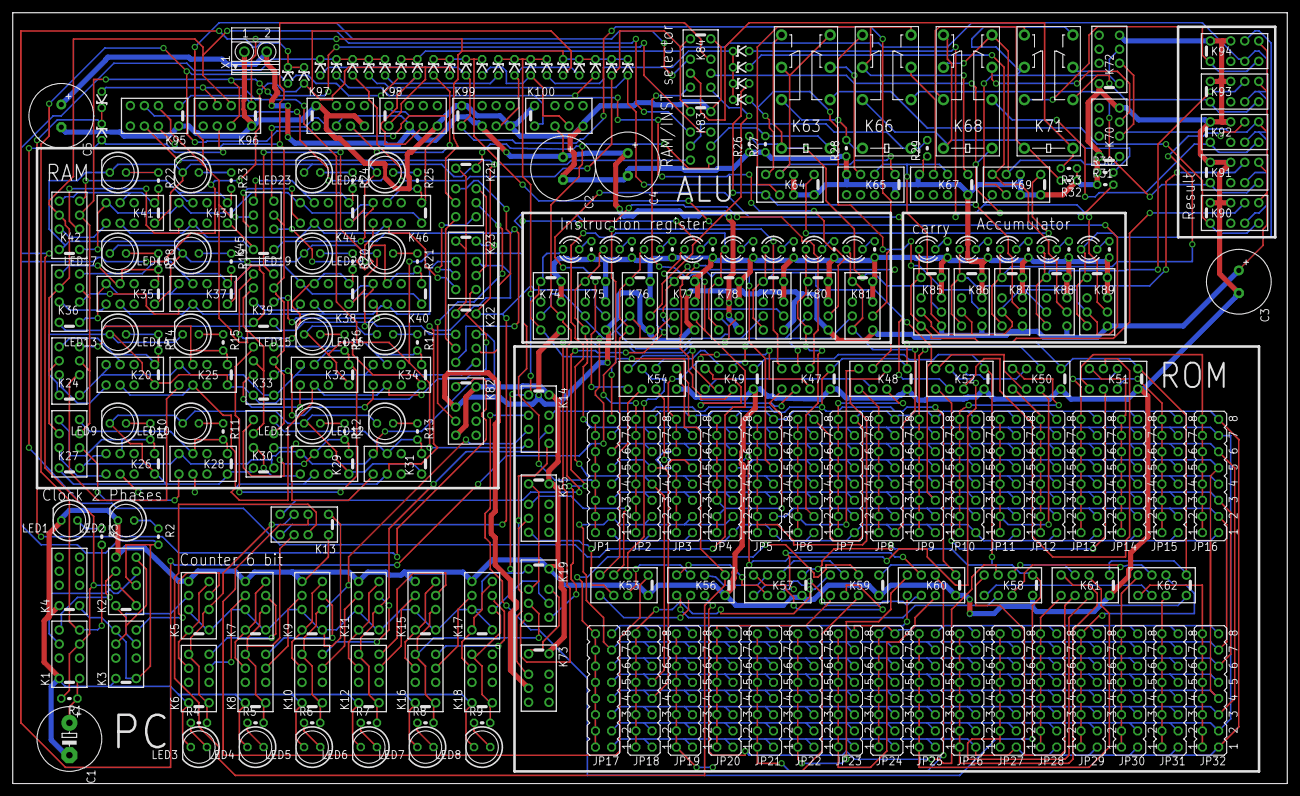
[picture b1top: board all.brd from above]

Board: 2 copper layers, 200.0 x 121.0 mm, 249 parts (0 on the bottom side), 252 nets.
